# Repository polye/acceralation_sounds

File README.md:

# acceralation_sounds
for 6wp

2019/05/10
velocity_testを追加
重力成分をカット
加速度から速度算出に成功？no

2019/05/13
velocity_test_0513を追加
速度算出は出来た。
誤差が多く乗ってずれていくので０に収束するようにloopごとに各成分＊beta(0.9)

**振り上げの時に前成分が乗ってしまう問題がある。

speaker_testを追加
DFPlayer_Mini_Mp3が使えなかったのでDFRobotDFPlayerMini.hを使用
9V電池で無事に動作

参考
https://www.wwwmaplesyrup-cs6.work/entry/2019/02/10/152415
DFPlayer_mini_mp3について、現在は非推奨とのこと
http://ogimotokin.hatenablog.com/entry/2019/01/24/015536

2019/05/14
2019/05/15
2019/05/16
2019/05/14

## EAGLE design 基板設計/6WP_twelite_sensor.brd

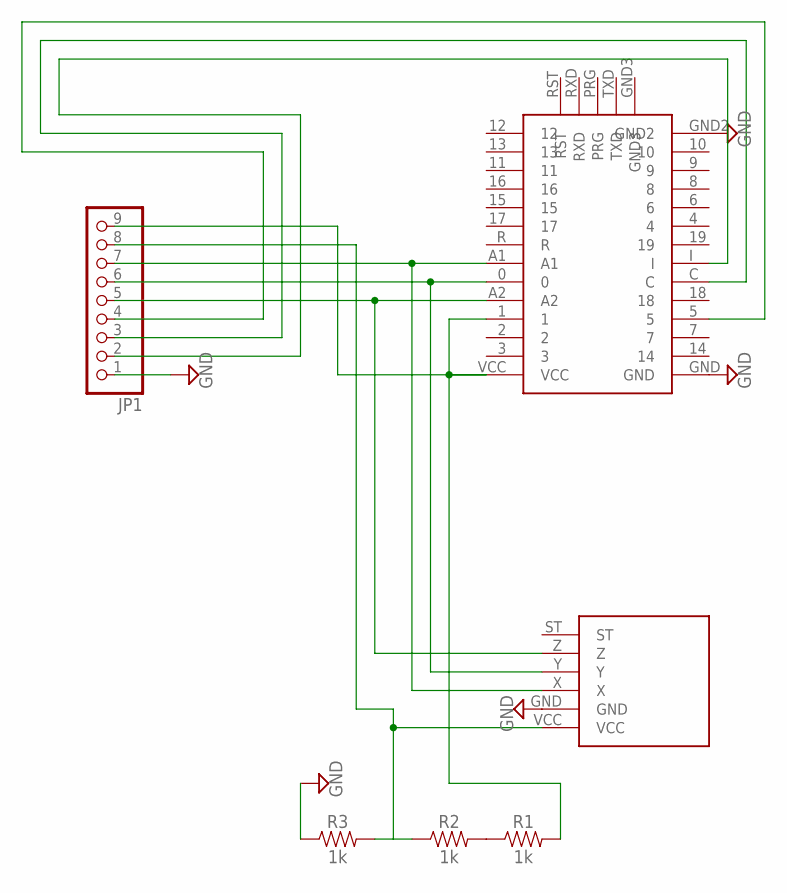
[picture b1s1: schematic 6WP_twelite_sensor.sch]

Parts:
A2: ADXL335
A4: TWELITEDIP
JP1: PINHD-1X9/90; 1X09/90
R1, R2, R3: 1k; AXIAL-0.3

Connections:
GND: A2.GND, A4.GND, A4.GND2, JP1.1, R3.P$1 (1)
unnamed: R1.P$1 (1), R2.P$2 (2)
unnamed: A4.C, JP1.3
unnamed: A4.1, A4.VCC, JP1.9, R1.P$2 (2)
unnamed: A2.Y, A4.0, JP1.6
unnamed: A2.Z, A4.A2, JP1.5
unnamed: A2.X, A4.A1, JP1.7
unnamed: A4.5, JP1.4
unnamed: A4.I, JP1.2
unnamed: A2.VCC, JP1.8, R2.P$1 (1), R3.P$2 (2)

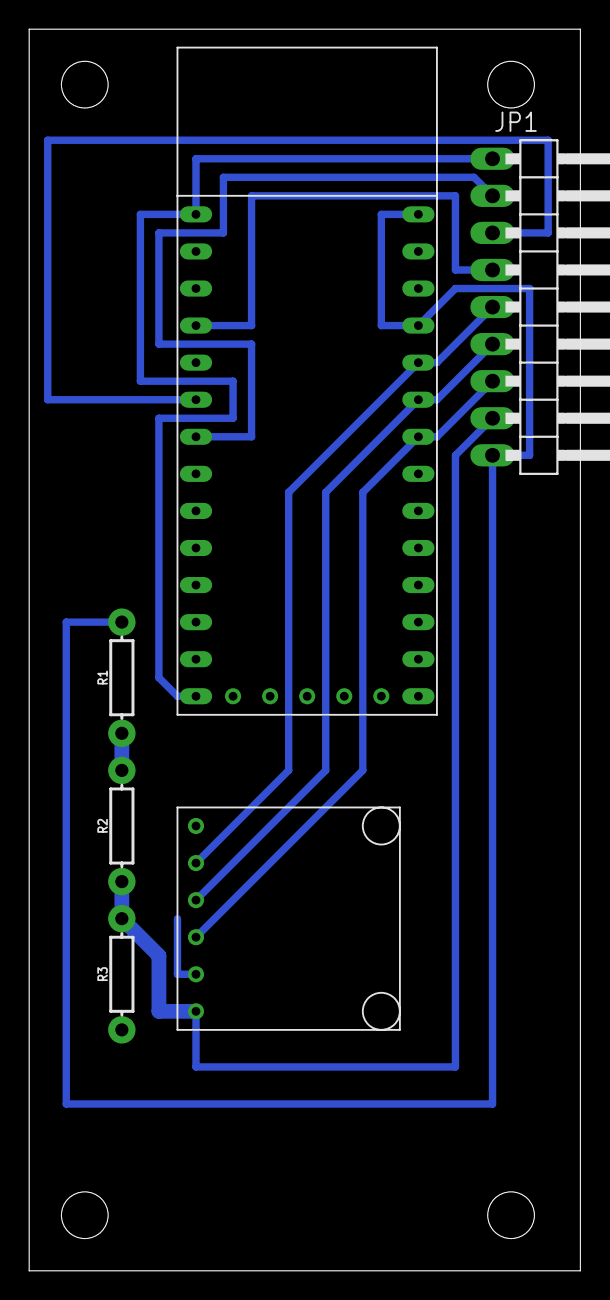
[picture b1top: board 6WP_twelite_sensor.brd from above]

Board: 2 copper layers, 37.8 x 85.1 mm, 6 parts (0 on the bottom side), 10 nets.

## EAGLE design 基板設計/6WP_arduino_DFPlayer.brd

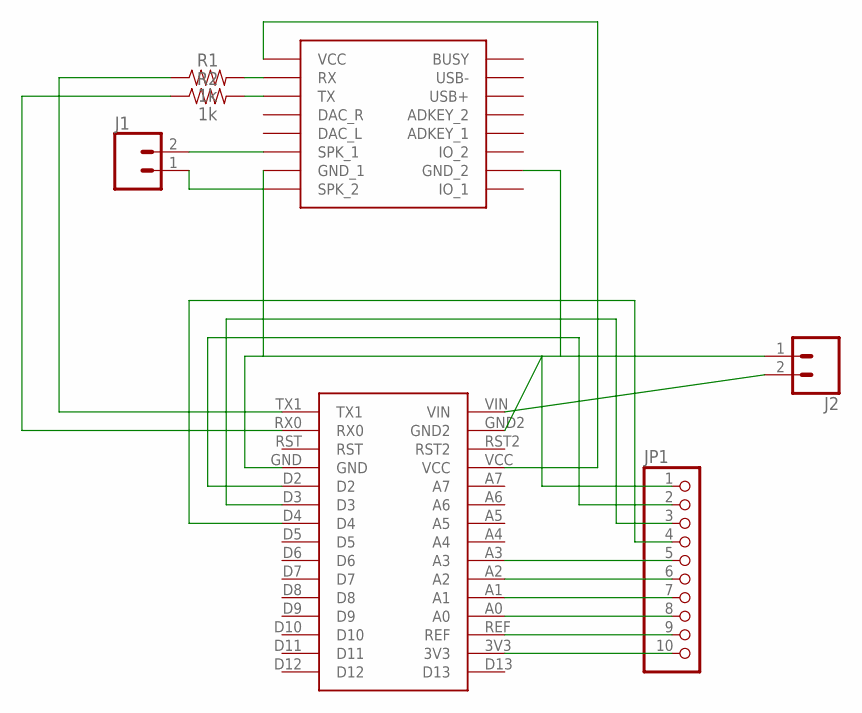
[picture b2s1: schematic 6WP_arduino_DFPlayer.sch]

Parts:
A3: ARDUINONANO
J1, J2: CONN_02JST-PTH-2; JST-2-PTH
JP1: PINHD-1X10/90; 1X10/90
R1, R2: 1k; AXIAL-0.3
U$1: DFPLAYER

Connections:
3V3: A3.3V3, JP1.10
A0: A3.A0, JP1.8
A1: A3.A1, JP1.7
A2: A3.A2, JP1.6
A3: A3.A3, JP1.5
D2: A3.D2, JP1.2
D3: A3.D3, JP1.3
D4: A3.D4, JP1.4
GND: A3.GND, A3.GND2, J2.1, JP1.1, U$1.GND_1, U$1.GND_2
unnamed: J1.2, U$1.SPK1 (SPK_1)
unnamed: J1.1, U$1.SPK2 (SPK_2)
unnamed: A3.VIN, J2.2
unnamed: R1.P$2 (2), U$1.RX
unnamed: A3.RX0, R2.P$1 (1)
unnamed: A3.TX1, R1.P$1 (1)
unnamed: R2.P$2 (2), U$1.TX
unnamed: A3.VCC, U$1.VCC
REF: A3.REF, JP1.9

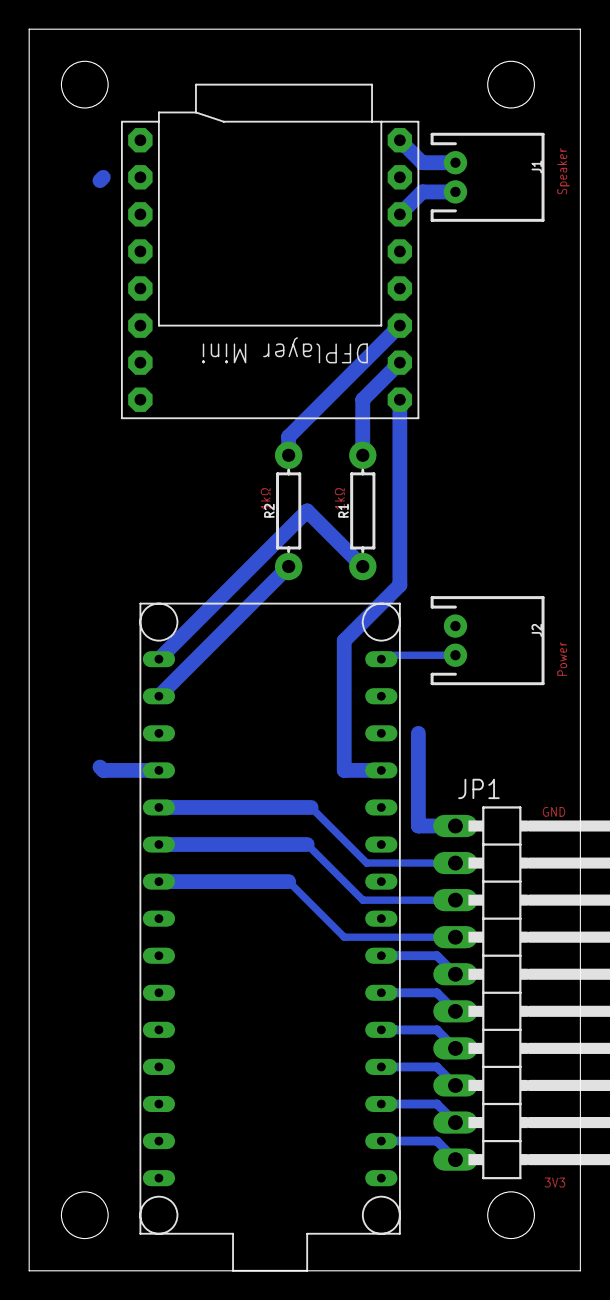
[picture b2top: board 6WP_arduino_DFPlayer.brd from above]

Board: 2 copper layers, 37.8 x 85.1 mm, 7 parts (0 on the bottom side), 18 nets.

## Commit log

2019-05-11 Create 基板設計

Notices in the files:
parts and their libraries:
SparkFun-Connectors: Licensing: Creative Commons ShareAlike 4.0 International - https://creativecommons.org/licenses/by-sa/4.0
